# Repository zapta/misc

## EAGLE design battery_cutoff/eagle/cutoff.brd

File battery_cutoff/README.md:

Arduino car battery monitor/cutoff.

This is a custom Arduino board that monitors and controsl 12V DC in car environment.
It contains an ATMEGA328P MCU that monitors the battery voltage and controls an output
relay. 

The Arduino sketch that I am using with this board detects engine cranking pattern on the 
battery line and disconnects the output voltage to the streaming BT adapter for 
1 second. This resets the BT adapter and causes it to pair with my phone (the 
12VDC socket in my car mentain power even after I turn the engine off which causes
the BT adapter not to pair with my phone when I come back to the car).

The board is not specific to this applictaion and with different sketch can do
other battery monitoring/cutoff operations.

The board is compatible with the Arduino IDE (it acts as an Arduino Mini Pro 5V 16Mhz).

The 3d subdirectory here includes a model for a 3d printable snap-on enclosure. You
can find there both the OpenSCAD source file and the gnerated STL file. The PCB 
is attached to the base of the encolsure using a double side 3M adhesive tape 
such as this one https://www.amazon.com/dp/B00OI6E0L2 .

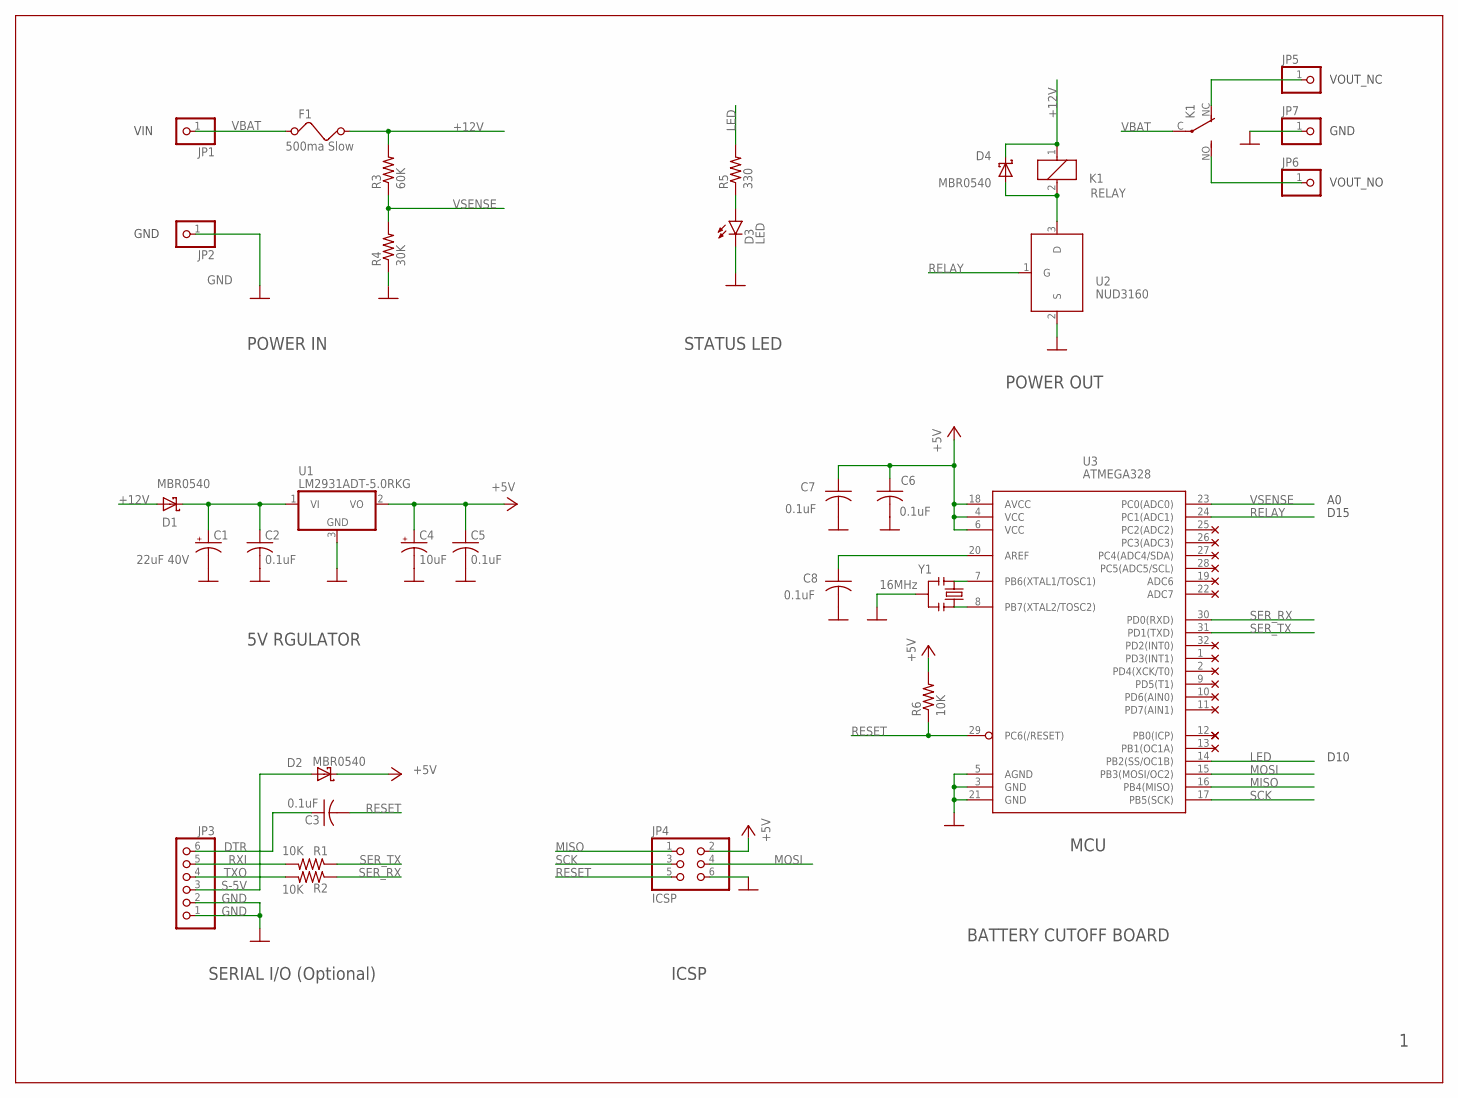
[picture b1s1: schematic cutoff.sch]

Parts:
C1: 22uF 40V; UD-6,3X5,8_NICHICON
C2, C3, C5, C6, C7, C8: 0.1uF; C0603K
C4: 10uF; A/3216-18R
D1, D2, D4: MBR0540; SOD123FL
D3: LED
F1: 500ma Slow; 1206
JP1, JP2, JP5, JP6, JP7: WIRE_PAD
JP3: PINHD-1X6; 1X06
JP4: ICSP; 2X03
K1: RELAY
R1, R2, R6: 10K; R0402
R3: 60K; R0402
R4: 30K; R0402
R5: 330; R0402
U1: LM2931ADT-5.0RKG; LDO
U2: NUD3160; SOT23
U3: ATMEGA328; TQFP32-08
Y1: 16MHz; RESONATOR-SMD

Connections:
+5V: C4.+, C5.1, C6.1, C7.1, D2.C, JP4.2, R6.2, U1.2 (VO), U3.4 (VCC), U3.6 (VCC), U3.18 (AVCC)
+12V: D1.A, D4.C, F1.2, K1.1, R3.2
AREF: C8.1, U3.20 (AREF)
DTR: C3.1, JP3.6
GND: C1.-, C2.2, C4.-, C5.2, C6.2, C7.2, C8.2, D3.K (C), JP2.1, JP3.1, JP3.2, JP4.6, JP7.1, R4.1, U1.3 (GND), U2.2 (S), U3.3 (GND), U3.5 (AGND), U3.21 (GND), Y1.2
LED: R5.2, U3.14 (PB2(SS/OC1B))
MISO: JP4.1, U3.16 (PB4(MISO))
MOSI: JP4.4, U3.15 (PB3(MOSI/OC2))
unnamed: D4.A, K1.2, U2.3 (D)
unnamed: D3.A, R5.1
unnamed: JP6.1, K1.NO (S)
unnamed: JP5.1, K1.NC (O)
unnamed: C1.+, C2.1, D1.C, U1.1 (VI)
RELAY: U2.1 (G), U3.24 (PC1(ADC1))
RESET: C3.2, JP4.5, R6.1, U3.29 (PC6(/RESET))
RXI: JP3.5, R1.2
S-5V: D2.A, JP3.3
SCK: JP4.3, U3.17 (PB5(SCK))
SER_RX: R2.1, U3.30 (PD0(RXD))
SER_TX: R1.1, U3.31 (PD1(TXD))
TXO: JP3.4, R2.2
VBAT: F1.1, JP1.1, K1.C
VSENSE: R3.1, R4.2, U3.23 (PC0(ADC0))
XTAL1: U3.7 (PB6(XTAL1/TOSC1)), Y1.3
XTAL2: U3.8 (PB7(XTAL2/TOSC2)), Y1.1

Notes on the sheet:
ICSP
SERIAL I/O (Optional)
MCU
STATUS LED
BATTERY CUTOFF BOARD
POWER IN
POWER OUT
5V RGULATOR
D15
D10
VOUT_NC
GND
VOUT_NO
VIN

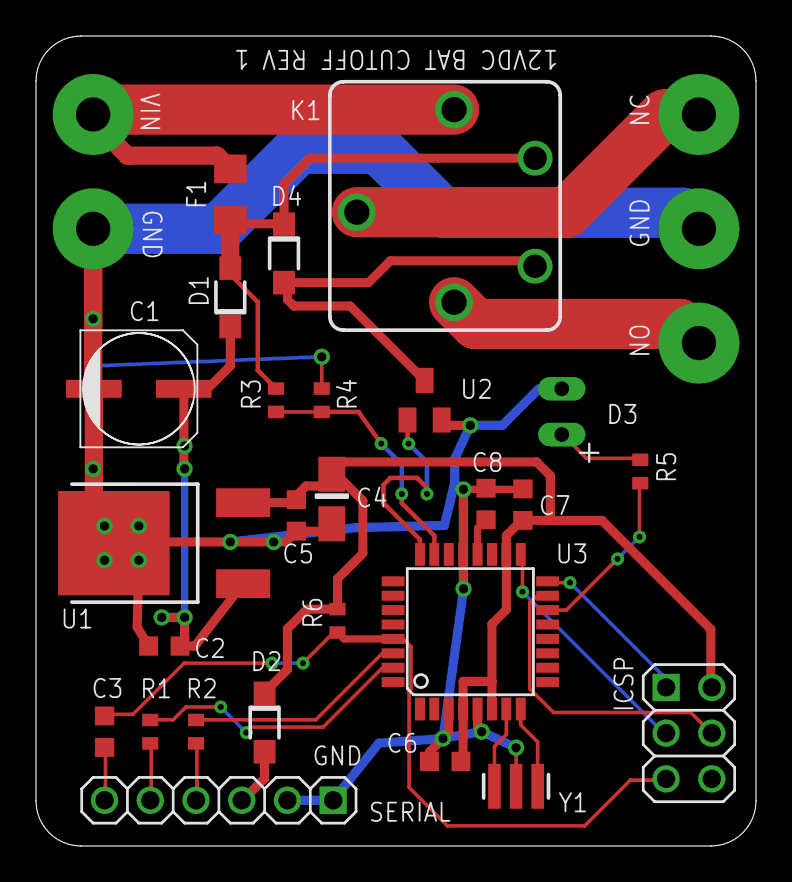
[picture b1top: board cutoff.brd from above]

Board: 2 copper layers, 40.0 x 45.0 mm, 31 parts (0 on the bottom side), 25 nets.

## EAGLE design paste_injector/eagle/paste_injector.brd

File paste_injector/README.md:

Arduino Motorized SMT Solder Paste Dispenser

3D model and general instructions are available on Thingiverse http://www.thingiverse.com/thing:1119914

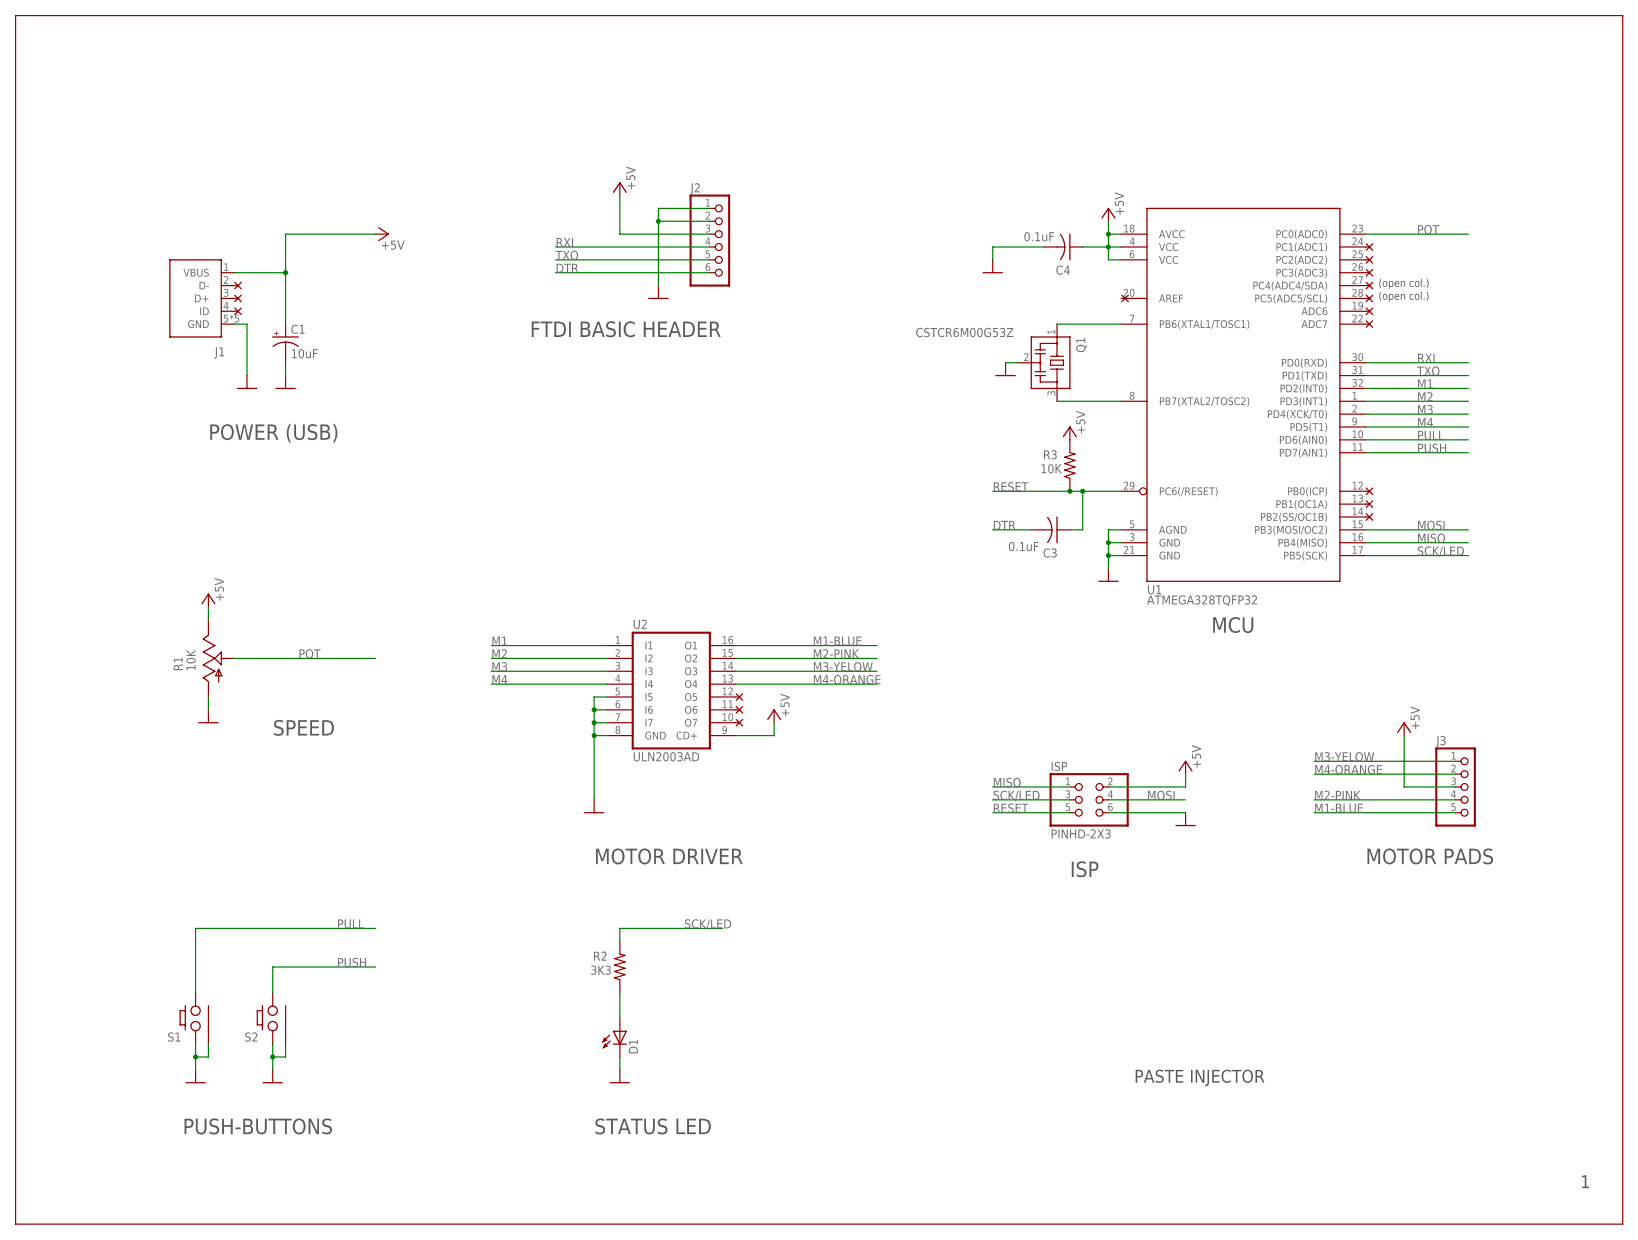
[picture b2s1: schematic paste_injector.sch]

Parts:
C1: 10uF; A/3216-18R
C3, C4: 0.1uF; C0603
D1: LED; LED0603
ISP: PINHD-2X3; 2X03
J1: USB; USB-MICRO-ZX62RD-AB-5P8
J2: PINHD-1X6; 1X06
J3: PINHD-1X5; 1X05
Q1: CSTCR6M00G53Z; CSTCR6M
R1: 10K; TRIMPOT
R2: 3K3; R0603
R3: 10K; R0603
S1, S2: PUSH_BUTTON
U1: ATMEGA328TQFP32; TQFP32-08
U2: ULN2003AD; SO16

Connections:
+5V: C1.+, C4.1, ISP.2, J1.1 (VBUS), J2.3, J3.3, R1.CW, R3.2, U1.4 (VCC), U1.6 (VCC), U1.18 (AVCC), U2.9 (CD+)
DTR: C3.2, J2.6
GND: C1.-, C4.2, D1.C, ISP.6, J1.5 (GND), J1.A (GND), J1.B (GND), J1.C (GND), J1.D (GND), J2.1, J2.2, Q1.2, R1.CCW, S1.A1 (1), S1.GND, S2.A1 (1), S2.GND, U1.3 (GND), U1.5 (AGND), U1.21 (GND), U2.5 (I5), U2.6 (I6), U2.7 (I7), U2.8 (GND)
M1: U1.32 (PD2(INT0)), U2.1 (I1)
M1-BLUE: J3.5, U2.16 (O1)
M2: U1.1 (PD3(INT1)), U2.2 (I2)
M2-PINK: J3.4, U2.15 (O2)
M3: U1.2 (PD4(XCK/T0)), U2.3 (I3)
M3-YELOW: J3.1, U2.14 (O3)
M4: U1.9 (PD5(T1)), U2.4 (I4)
M4-ORANGE: J3.2, U2.13 (O4)
MISO: ISP.1, U1.16 (PB4(MISO))
MOSI: ISP.4, U1.15 (PB3(MOSI/OC2))
unnamed: D1.A, R2.1
unnamed: Q1.1, U1.7 (PB6(XTAL1/TOSC1))
unnamed: Q1.3, U1.8 (PB7(XTAL2/TOSC2))
POT: R1.C, U1.23 (PC0(ADC0))
PULL: S1.B1 (2), U1.10 (PD6(AIN0))
PUSH: S2.B1 (2), U1.11 (PD7(AIN1))
RESET: C3.1, ISP.5, R3.1, U1.29 (PC6(/RESET))
RXI: J2.4, U1.30 (PD0(RXD))
SCK/LED: ISP.3, R2.2, U1.17 (PB5(SCK))
TXO: J2.5, U1.31 (PD1(TXD))

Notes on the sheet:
PASTE INJECTOR
ISP
POWER (USB)
SPEED
MOTOR DRIVER
MCU
MOTOR PADS
(open col.)
FTDI BASIC HEADER
STATUS LED
PUSH-BUTTONS

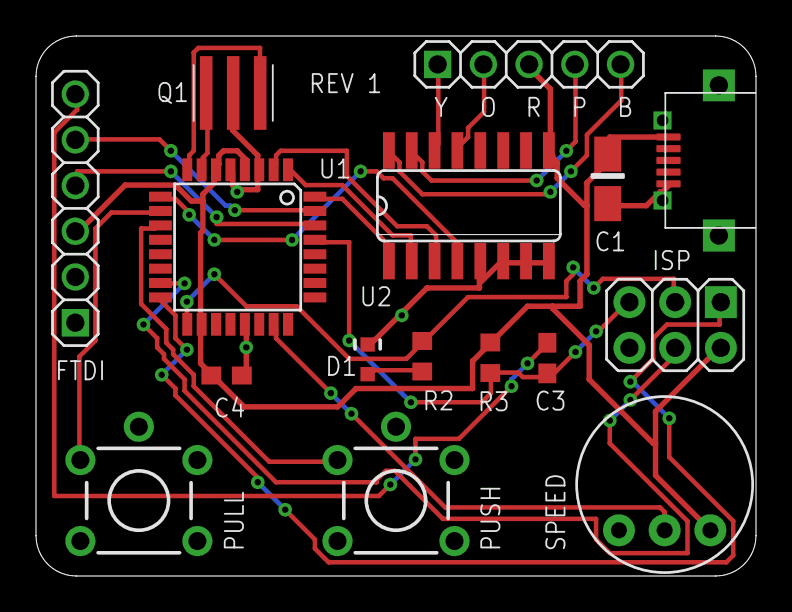
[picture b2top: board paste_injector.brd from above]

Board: 2 copper layers, 40.0 x 30.0 mm, 16 parts (0 on the bottom side), 23 nets.

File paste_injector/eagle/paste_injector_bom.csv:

Quantity,Description,Part Designators,Digikey Part Number,Manufacturer Name,Manufacturer Part Number,Comments1,3.3K 5% 1/10W 0603,R2,311-3.3KGRCT-ND,Yageo,RC0603JR-073K3L,1,10K 5%  1/10W 0603,R3,311-10KGRCT-ND,Yageo,RC0603JR-0710KL,2,0.1uf ceramic 10% 25V 0603,C3  C4,311-1344-1-ND,Yageo,CC0603KRX7R9BB104,1,LED Red 0603,D1,475-2512-1-ND,OSRAM Opto Semiconductors Inc.,LS Q976-NR-1,1,Micro USB connector,J1,H11611CT-ND,ZX62RD-AB-5P8,Hirose Electric Co Ltd,1,Trimpot 10K,R1,987-1167-ND,TT Electronics/BI,91AR10KLF,1,ATMEGA328P TQFP32,U1,ATMEGA328P-AURCT-ND,Atmel,ATMEGA328P-AUR,1,Resonator 16Mhz w/caps,Q1,535-10008-1-ND,Abracon LLC,AWSCR-16.00CV-T,1,ULN2003A  SOIC,U2,296-1368-1-ND,Texas Instruments,ULN2003ADR,2,Push Button,S1  S2,P8014S-ND,Panasonic Electronic Components,EVQ-PBC05R,1,Tantalum cap 10uF 10%  16V 1206,C1,399-3684-1-ND,Kemet,T491A106K010AT,1,5V bipolar geared stepper motor ,,,,28BYJ-48,Ebay7,Taper M4 heat threaded insert,,,McMaster,94180a353,2,M3 10mm socket head cup screw,,,McMaster,91274a105,Generic2,M3 nut,,,McMaster,94150a325,Generic4,M4 10mm socket head cup screw,,,McMaster,91274A117,Generic1,M4 0.7 x 64mm threaded rod,,,McMaster,90024a222,Cut to length1,10ml luer lock syringe,,,BD,REF309604,"Bectron, Dickinson"

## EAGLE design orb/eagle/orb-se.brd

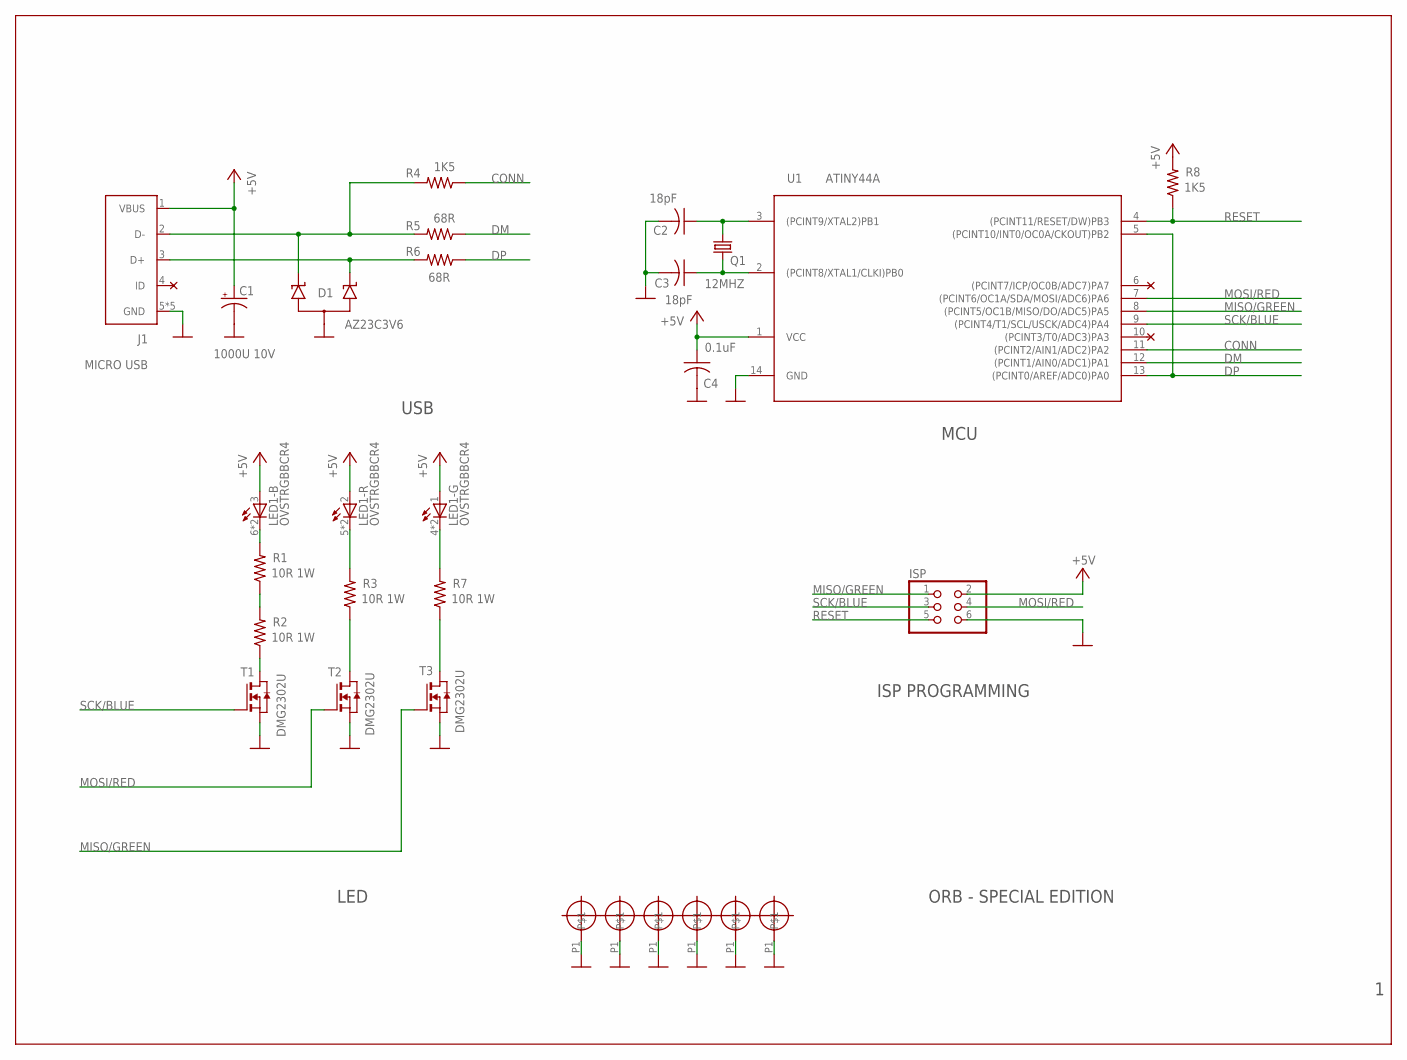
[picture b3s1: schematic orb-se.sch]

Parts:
C1: 1000U 10V; 153CLV-1010
C2, C3: 18pF; C0805
C4: 0.1uF; C0805
D1: AZ23C3V6; SOT23
ISP: PINHD-2X3; 2X03
J1: MICRO USB; USB-MICRO
LED1: OVSTRGBBCR4
MH$1, MH$2, MH$3, MH$4, MH$5, MH$6: MOUNTING_HOLE
Q1: 12MHZ; CRYSTAL
R1, R2, R3, R7: 10R 1W; R2512W
R4, R8: 1K5; R0805
R5, R6: 68R; R0805
T1, T2, T3: DMG2302U; SOT-23
U1: ATINY44A; SOIC14

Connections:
+5V: C1.+, C4.1, ISP.2, J1.1 (VBUS), LED1.1 (A), LED1.2 (A), LED1.3 (A), R8.2, U1.1 (VCC)
CONN: R4.1, U1.11 ((PCINT2/AIN1/ADC2)PA2)
DM: R5.1, U1.12 ((PCINT1/AIN0/ADC1)PA1)
DP: R6.1, U1.5 ((PCINT10/INT0/OC0A/CKOUT)PB2), U1.13 ((PCINT0/AREF/ADC0)PA0)
GND: C1.-, C2.2, C3.2, C4.2, D1.3 (AA), ISP.6, J1.5 (GND), J1.G1 (GND), J1.G2 (GND), J1.G3 (GND), J1.G4 (GND), MH$1.P1, MH$2.P1, MH$3.P1, MH$4.P1, MH$5.P1, MH$6.P1, T1.2 (S), T2.2 (S), T3.2 (S), U1.14 (GND)
MISO/GREEN: ISP.1, T3.3 (G), U1.8 ((PCINT5/OC1B/MISO/DO/ADC5)PA5)
MOSI/RED: ISP.4, T2.3 (G), U1.7 ((PCINT6/OC1A/SDA/MOSI/ADC6)PA6)
unnamed: C2.1, Q1.2, U1.3 ((PCINT9/XTAL2)PB1)
unnamed: C3.1, Q1.1, U1.2 ((PCINT8/XTAL1/CLKI)PB0)
unnamed: R1.1, R2.2
unnamed: D1.1 (K1), J1.2 (D-), R4.2, R5.2
unnamed: D1.2 (K2), J1.3 (D+), R6.2
unnamed: LED1.6 (C), LED1.6@1 (C), R1.2
unnamed: LED1.5 (C), LED1.5@1 (C), R3.2
unnamed: LED1.4 (C), LED1.4@1 (C), R7.2
unnamed: R2.1, T1.1 (D)
unnamed: R3.1, T2.1 (D)
unnamed: R7.1, T3.1 (D)
RESET: ISP.5, R8.1, U1.4 ((PCINT11/RESET/DW)PB3)
SCK/BLUE: ISP.3, T1.3 (G), U1.9 ((PCINT4/T1/SCL/USCK/ADC4)PA4)

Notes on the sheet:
ORB - SPECIAL EDITION
USB
MCU
ISP PROGRAMMING
LED

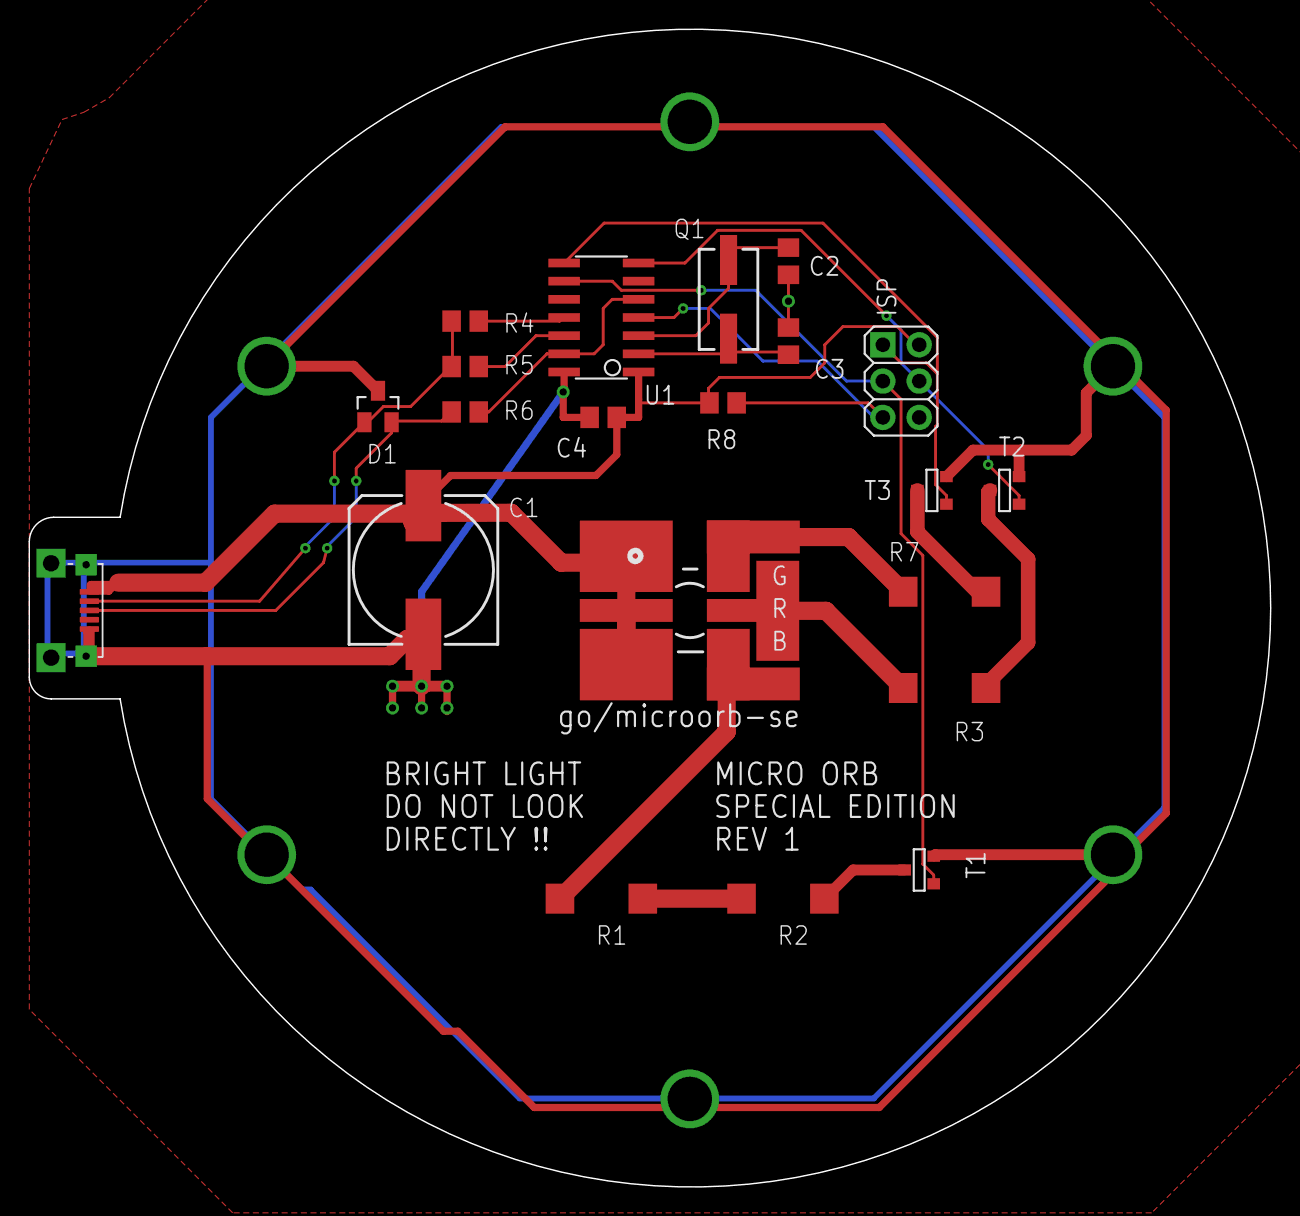
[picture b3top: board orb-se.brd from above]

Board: 2 copper layers, 86.8 x 80.9 mm, 27 parts (0 on the bottom side), 20 nets.

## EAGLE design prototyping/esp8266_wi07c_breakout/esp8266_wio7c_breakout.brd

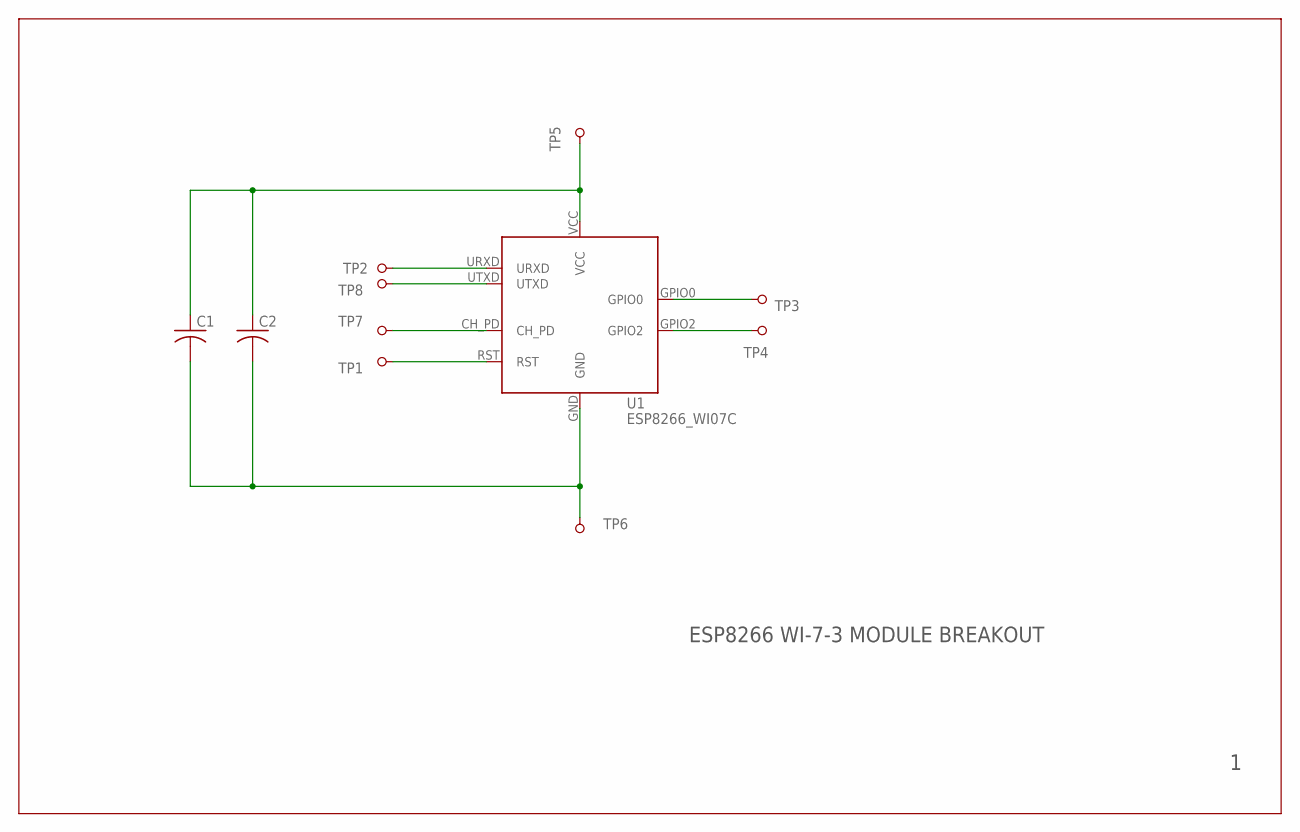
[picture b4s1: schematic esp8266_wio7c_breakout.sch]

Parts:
C1, C2: CAPACITORC0603K; C0603K
TP1, TP2, TP3, TP4, TP5, TP7, TP8: PINHD-1X1; 1X01
TP6: PINHD-1X1-FIRST; 1X01_FIRST
U1: ESP8266_WI07C

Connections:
CH_PD: TP7.1, U1.CH_PD
GND: C1.2, C2.2, TP6.1, U1.GND
GPIO0: TP3.1, U1.GPIO0
GPIO2: TP4.1, U1.GPIO2
RST: TP1.1, U1.RST
URXD: TP2.1, U1.URXD
UTXD: TP8.1, U1.UTXD
VCC: C1.1, C2.1, TP5.1, U1.VCC

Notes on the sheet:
ESP8266 WI-7-3 MODULE BREAKOUT

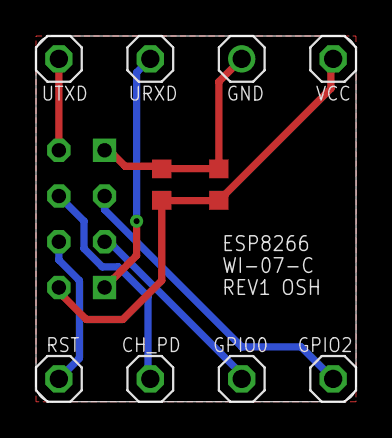
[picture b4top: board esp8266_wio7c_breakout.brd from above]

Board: 2 copper layers, 17.8 x 20.3 mm, 11 parts (0 on the bottom side), 8 nets.

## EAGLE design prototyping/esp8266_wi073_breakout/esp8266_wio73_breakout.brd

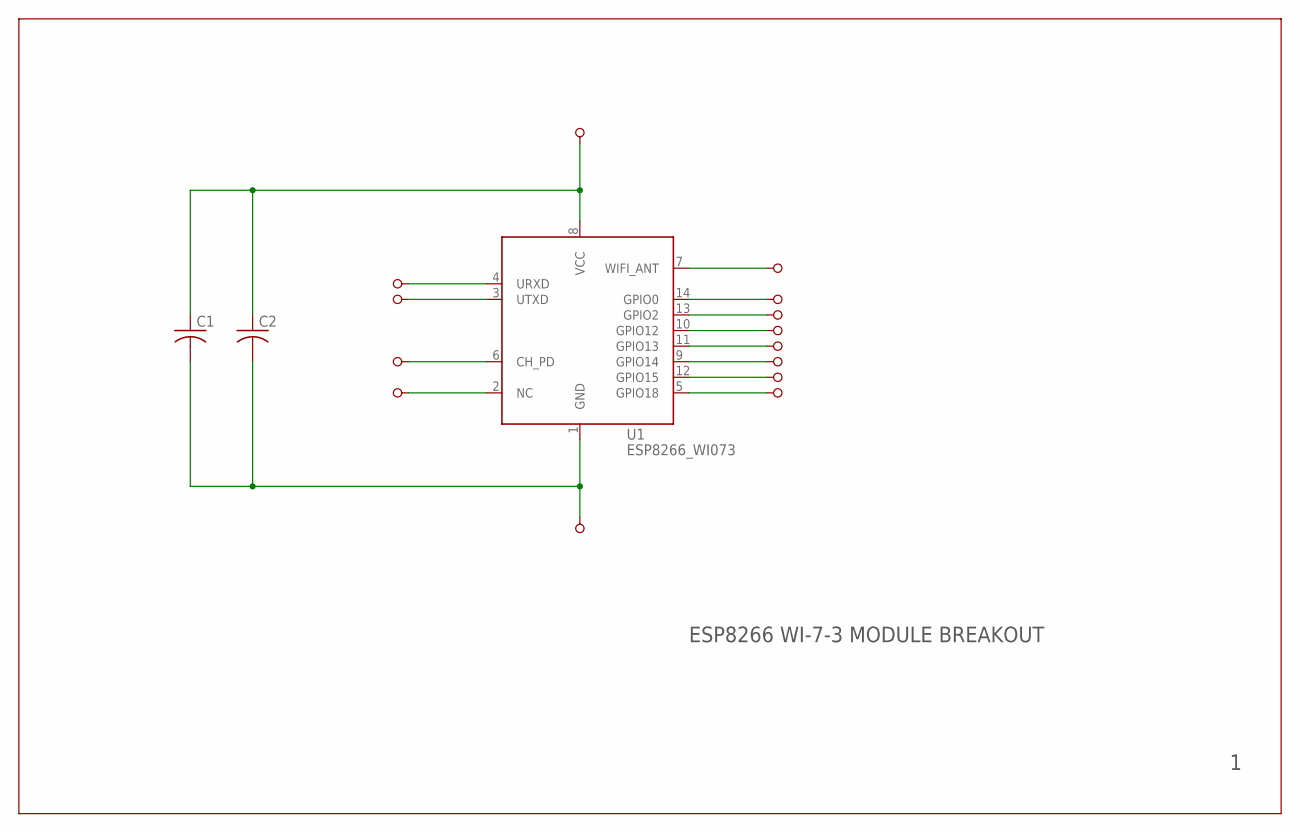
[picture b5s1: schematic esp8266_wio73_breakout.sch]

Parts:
C1, C2: CAPACITORC0603K; C0603K
TP1: PINHD-1X1-FIRST; 1X01_FIRST
TP2, TP3, TP4, TP5, TP6, TP7, TP8, TP9, TP10, TP11, TP12, TP13, TP14: PINHD-1X1; 1X01
U1: ESP8266_WI073

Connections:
GND: C1.2, C2.2, TP1.1, U1.1 (GND)
unnamed: TP4.1, U1.4 (URXD)
unnamed: TP3.1, U1.3 (UTXD)
unnamed: TP6.1, U1.6 (CH_PD)
unnamed: TP2.1, U1.2 (NC)
unnamed: TP7.1, U1.7 (WIFI_ANT)
unnamed: TP14.1, U1.14 (GPIO0)
unnamed: TP13.1, U1.13 (GPIO2)
unnamed: TP10.1, U1.10 (GPIO12)
unnamed: TP11.1, U1.11 (GPIO13)
unnamed: TP9.1, U1.9 (GPIO14)
unnamed: TP12.1, U1.12 (GPIO15)
unnamed: TP5.1, U1.5 (GPIO18)
VCC: C1.1, C2.1, TP8.1, U1.8 (VCC)

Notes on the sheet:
ESP8266 WI-7-3 MODULE BREAKOUT

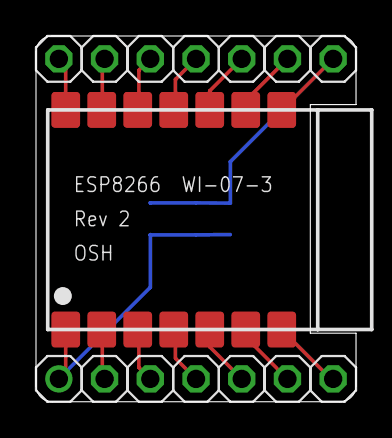
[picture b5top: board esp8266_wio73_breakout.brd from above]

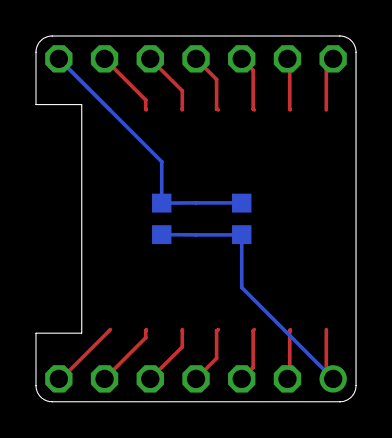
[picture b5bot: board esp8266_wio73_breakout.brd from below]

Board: 2 copper layers, 17.8 x 20.3 mm, 17 parts (2 on the bottom side), 14 nets.

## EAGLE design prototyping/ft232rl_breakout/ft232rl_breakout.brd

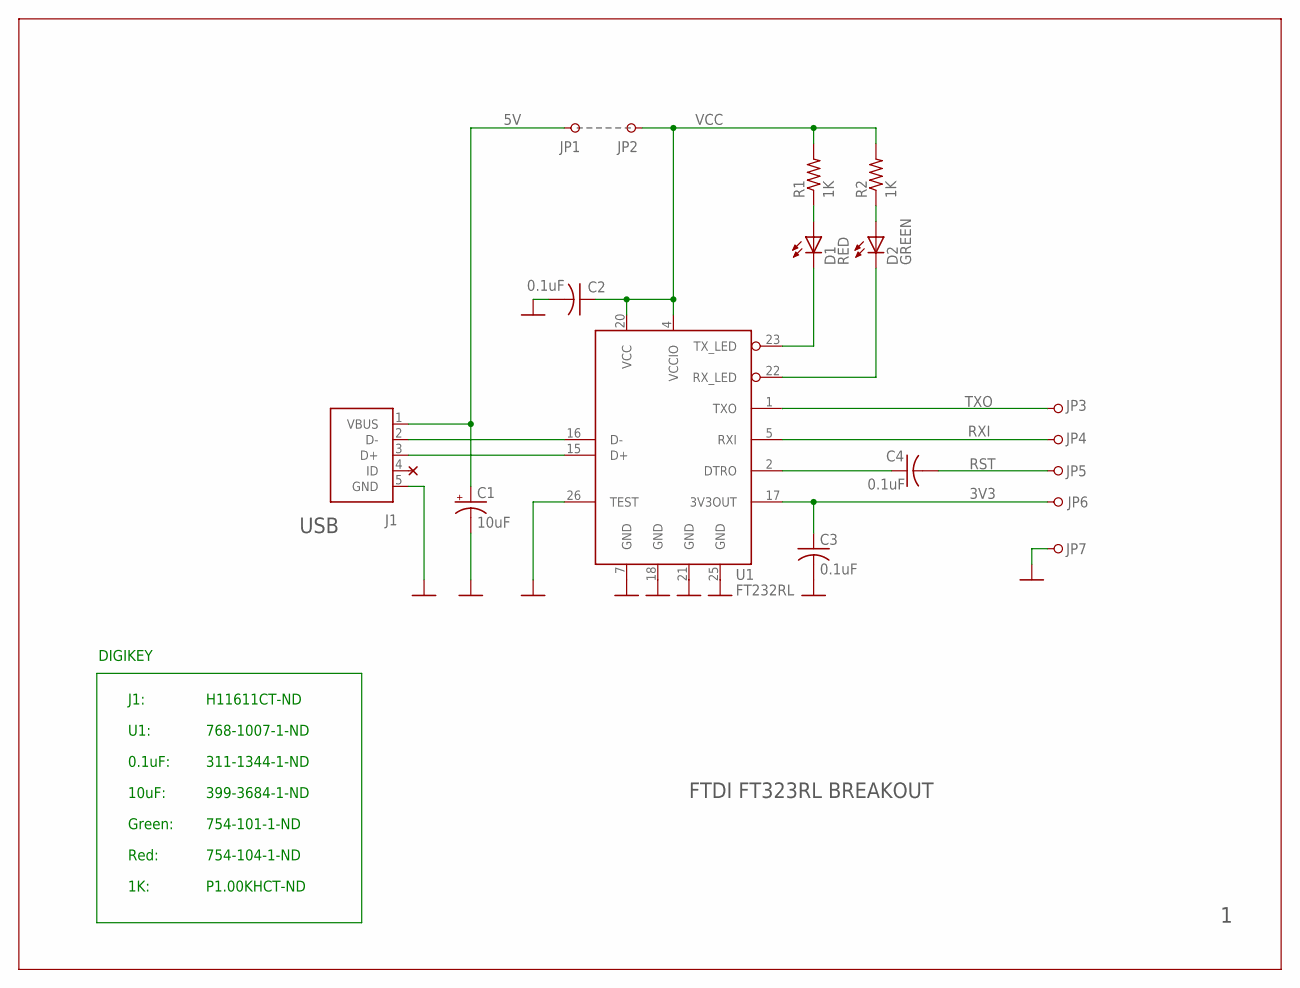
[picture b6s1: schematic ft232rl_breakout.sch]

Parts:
C1: 10uF; A/3216-18R
C2, C3, C4: 0.1uF; C0402K
D1: RED; LED_0402
D2: GREEN; LED_0402
J1: USB; USB-MICRO-ZX62RD-AB-5P8
JP1, JP2, JP3, JP4, JP5, JP6, JP7: PINHD-1X1; 1X01
R1, R2: 1K; R0402
U1: FT232RL; SSOP28DB

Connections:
3V3: C3.1, JP6.1, U1.17 (3V3OUT)
5V: C1.+, J1.1 (VBUS), JP1.1
GND: C1.-, C2.2, C3.2, J1.5 (GND), JP7.1, U1.7 (GND), U1.18 (GND), U1.21 (GND), U1.25 (GND), U1.26 (TEST)
unnamed: D1.C, U1.23 (TX_LED)
unnamed: D2.C, U1.22 (RX_LED)
unnamed: D1.A, R1.1
unnamed: D2.A, R2.1
unnamed: J1.3 (D+), U1.15 (D+)
unnamed: C4.1, U1.2 (DTRO)
unnamed: J1.2 (D-), U1.16 (D-)
RST: C4.2, JP5.1
RXI: JP4.1, U1.5 (RXI)
TXO: JP3.1, U1.1 (TXO)
VCC: C2.1, JP2.1, R1.2, R2.2, U1.4 (VCCIO), U1.20 (VCC)

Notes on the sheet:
FTDI FT323RL BREAKOUT
USB
J1:
U1:
0.1uF:
10uF:
Green:
Red:
1K:
H11611CT-ND
768-1007-1-ND
311-1344-1-ND
399-3684-1-ND
754-101-1-ND
754-104-1-ND
P1.00KHCT-ND
DIGIKEY

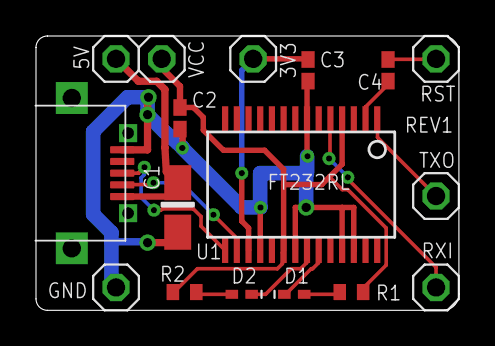
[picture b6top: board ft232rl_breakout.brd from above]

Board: 2 copper layers, 23.5 x 15.2 mm, 17 parts (0 on the bottom side), 14 nets.

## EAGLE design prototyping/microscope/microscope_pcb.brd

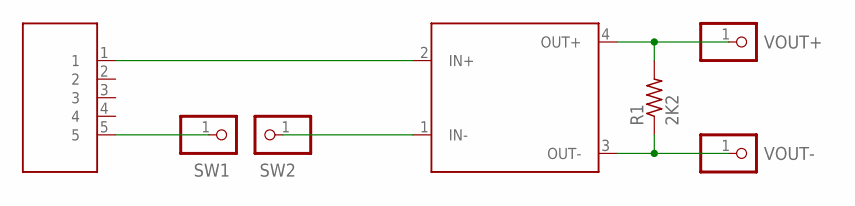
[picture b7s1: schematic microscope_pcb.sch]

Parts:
R1: 2K2; R0805
SW1, SW2: PINHD-1X1; 1X01
U$1: DC_DC
U$2: USB_CONNECTOR
VOUT+: PINHD-1X1; 1X01
VOUT-: PINHD-1X1; 1X01

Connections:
unnamed: R1.2, U$1.4 (OUT+), VOUT+.1
unnamed: R1.1, U$1.3 (OUT-), VOUT-.1
unnamed: U$1.2 (IN+), U$2.1
unnamed: SW1.1, U$2.5
unnamed: SW2.1, U$1.1 (IN-)

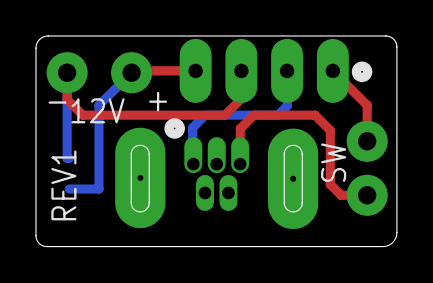
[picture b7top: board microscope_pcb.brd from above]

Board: 2 copper layers, 20.1 x 11.7 mm, 7 parts (1 on the bottom side), 5 nets.

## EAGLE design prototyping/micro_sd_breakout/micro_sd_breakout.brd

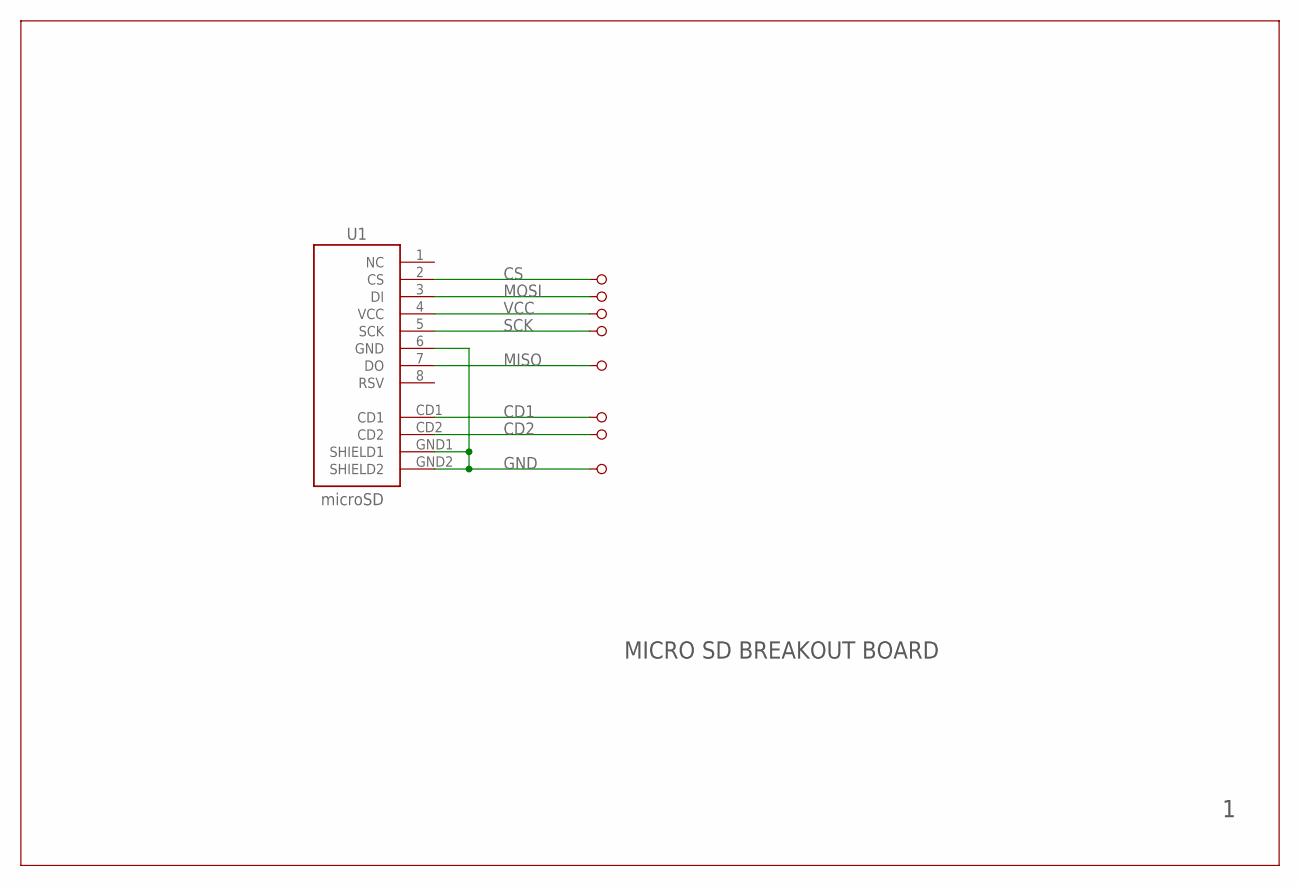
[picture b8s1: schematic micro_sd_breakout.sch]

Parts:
JP1, JP2, JP3, JP4, JP5, JP6, JP7, JP8: PINHD-1X1; 1X01
U1: microSD; MICRO-SD-SOCKET-PP

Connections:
CD1: JP6.1, U1.CD1
CD2: JP7.1, U1.CD2
CS: JP1.1, U1.2 (CS)
GND: JP8.1, U1.6 (GND), U1.GND1 (SHIELD1), U1.GND2 (SHIELD2)
MISO: JP5.1, U1.7 (DO)
MOSI: JP2.1, U1.3 (DI)
SCK: JP4.1, U1.5 (SCK)
VCC: JP3.1, U1.4 (VCC)

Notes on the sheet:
MICRO SD BREAKOUT BOARD

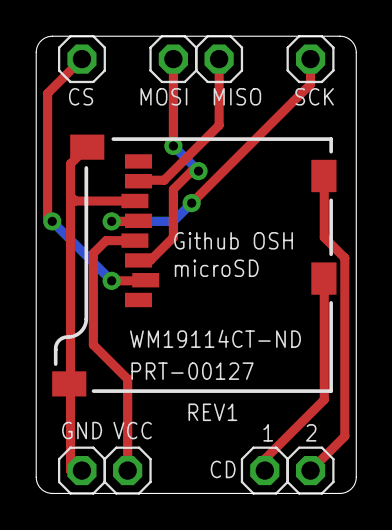
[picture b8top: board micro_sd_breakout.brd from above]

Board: 2 copper layers, 17.8 x 25.4 mm, 9 parts (0 on the bottom side), 8 nets.

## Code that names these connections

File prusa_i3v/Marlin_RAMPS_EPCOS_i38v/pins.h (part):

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*                        ATMega644
*
*                        +---\/---+
*            (D 0) PB0  1|        |40  PA0 (AI 0 / D31)
*            (D 1) PB1  2|        |39  PA1 (AI 1 / D30)
*       INT2 (D 2) PB2  3|        |38  PA2 (AI 2 / D29)
*        PWM (D 3) PB3  4|        |37  PA3 (AI 3 / D28)
*        PWM (D 4) PB4  5|        |36  PA4 (AI 4 / D27)
*       MOSI (D 5) PB5  6|        |35  PA5 (AI 5 / D26)
*       MISO (D 6) PB6  7|        |34  PA6 (AI 6 / D25)
*        SCK (D 7) PB7  8|        |33  PA7 (AI 7 / D24)
*                  RST  9|        |32  AREF
*                  VCC 10|        |31  GND 
*                  GND 11|        |30  AVCC
*                XTAL2 12|        |29  PC7 (D 23)
*                XTAL1 13|        |28  PC6 (D 22)
*       RX0 (D 8)  PD0 14|        |27  PC5 (D 21) TDI
*       TX0 (D 9)  PD1 15|        |26  PC4 (D 20) TDO
*  INT0 RX1 (D 10) PD2 16|        |25  PC3 (D 19) TMS
*  INT1 TX1 (D 11) PD3 17|        |24  PC2 (D 18) TCK
*       PWM (D 12) PD4 18|        |23  PC1 (D 17) SDA
*       PWM (D 13) PD5 19|        |22  PC0 (D 16) SCL
*       PWM (D 14) PD6 20|        |21  PD7 (D 15) PWM
*                        +--------+
*
****************************************************************************************/
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
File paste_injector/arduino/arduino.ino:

// Controller the solder paste injector.

// For motor pin connection see motor_io.cpp.

#include "motor.h"

// Finite state machine states. Using 8bit enums.
namespace states {
  // Not moving, motor is on.
  static const uint8_t IDLE = 0;
  // Moving forward as long as the forward button is pressed.
  // Speed is controlled by the potentiometer.
  static const uint8_t FORWARD = 1;
  // Moving backward at a fast speed as long as the Backward button
  // is pressed.
  static const uint8_t BACKWARD = 3;
  // Same as IDLE but motor coils are not energized.
  static const uint8_t SLEEP = 4;
};

static uint8_t state = states::IDLE;

// Arduino pin for nnboard LED. For debugging. Active high.
const int kLedPin = 13;

// Arduino potentiometer analog input pin.
static const int kPotPin = A0;

// Arduino input pin for the forward (push) button. Active low.
static const int kForwardButtonPin = 7;

// Arduino input pin for the backward (pull) button. Active low.
static const int kBackwardButtonPin = 6;

// After this idle time, the power to the motor is
// disconnected. 
static const uint32_t kSleepTimeMillis =20*1000;

// Speeds in steps/sec.
static const int kBackwardSpeed = 500;

// Time in millis since entering the current state.
static uint32_t current_state_start_time_millis = 0;

// TODO: why do we need this to compile. The function is just below.
//static void setState(uint8_t newState);

// A common function to change state.
static void setState(uint8_t newState) {
  if (newState != state) {
    Serial.print(state);
    Serial.print(" --> ");
    Serial.println(newState);
    state = newState;
    current_state_start_time_millis = millis();
  }
}

static inline uint32_t millisInCurrentState() {
  return (millis() - current_state_start_time_millis);
}

// Using this as a poor man debouncing in states that we entered
// due to a button action.
static inline boolean debouncingDelay() {
   return millisInCurrentState() >= 25;
}

// Consts of a single segment of the pot value mapping function.
struct MapSegment {
  const int inMin;
  const int inMax;
  const int outMin;
  const int outMax;
};

// Consts for all the segments of the pot value mapping function.
static const MapSegment kMapSegments[] = {
  {  0,   128,  1,    2},
  {128,   256,  2,    4},
  {256,   384,  4,   10},
  {384,   512, 10,   22},
  {512,  640,  22,   48},
  {640,  768,  48,  105},
  {768,  896, 105,  229},
  {896, 1023, 229,  500},
};

// NUmber of segments in kMapSegments.
const int kNumMapSegments = sizeof(kMapSegments) / sizeof(kMapSegments[0]);

// Map pot value to speed. We use an aproximation of a logarithmic
// function using the linear segments in kMapSegments.
int mapPotValue(int potValue) {
  potValue = constrain(potValue, 0, 1023);
  for (int i = 0; i < kNumMapSegments; i++) {
    const MapSegment& s = kMapSegments[i];
    if (potValue <= s.inMax) {
      // TODO: precompute dIn and dOut.
      return (int) (((long)potValue - s.inMin) * (s.outMax - s.outMin) / (s.inMax - s.inMin)) + s.outMin;
    }
  }
  return kMapSegments[kNumMapSegments - 1].outMax;
}

// These two are updated each time readPostAsSpeed() is called.
static unsigned long timeLastPotReadMillis = 0;
static int lastPotValueAsSpeed = 0;

// Read pot value and return it mapped to speed.
static int readPotAsSpeed() {
  timeLastPotReadMillis = millis();
  const int potValue = analogRead(kPotPin);
  lastPotValueAsSpeed = mapPotValue(potValue);
  Serial.print("S:");
  Serial.println(lastPotValueAsSpeed);
  return lastPotValueAsSpeed;
}

inline long millisSinceLastPotRead() {
  return millis() - timeLastPotReadMillis;
}

inline bool isForwardButtonPressed() {
  // TODO: debounce.
  //
  // Active low.
  return !digitalRead(kForwardButtonPin);
}

inline bool isBackwardButtonPressed() {
  // TODO: debounce.
  //
  // Active low.
  return !digitalRead(kBackwardButtonPin);
}

// Arduino initialization function.
void setup() {
  Serial.begin(115200);
  
  pinMode(kLedPin, OUTPUT);

  pinMode(kForwardButtonPin, INPUT_PULLUP);
  pinMode(kBackwardButtonPin, INPUT_PULLUP);

  motor::setup();
  motor::setSpeed(0, true);
}

// Arduino main loop function.
void loop() {  
  // Update the motor outputs as needed.
  motor::loop();

  // TODO: have a more interesting LED pattern. Currently it's on iff
  // in a state that turns the motor.
  digitalWrite(kLedPin, motor::isNonZeroSpeed());

  // Here when last motion operation is completed.
  switch (state) {
    case states::IDLE:
      if (millisInCurrentState() >= kSleepTimeMillis) {
        motor::sleep();
        setState(states::SLEEP);
        return;
      }
      // Handle buttons unly after minimal debouncing delay.
      if (!debouncingDelay()) {
        return;
      }
      //
      // Handle Forward button press.
      if (isForwardButtonPressed()) {
        motor::setSpeed(readPotAsSpeed(), true);
        setState(states::FORWARD);
        return;
      }
      // Handle Backward button press.
      if (isBackwardButtonPressed()) {
        motor::setSpeed(kBackwardSpeed, false);
        setState(states::BACKWARD);
        return;
      }
      break;

    case states::FORWARD:
      // Handle Forward button release.
      if (!isForwardButtonPressed() && debouncingDelay()) {
        motor::setSpeed(0, true);
        setState(states::IDLE);
        return;
      }
      // Handle pot changes.
      if (millisSinceLastPotRead() >= 250) {
        motor::setSpeed(readPotAsSpeed(), true);
      }
      break;

    case states::BACKWARD:
      // Handle Backward button release.
      if (!isBackwardButtonPressed() && debouncingDelay()) {
        motor::setSpeed(0, true);
        setState(states::IDLE);
        return;
      }
      break;

    case states::SLEEP:
      if (isForwardButtonPressed() || isBackwardButtonPressed()) {
        motor::setSpeed(0, false);
        setState(states::IDLE);
        return;  
      }
      break;

    default:
      // Should never happend.
      Serial.println("Unknown state");
      // This also prints the unknown state.
      setState(states::IDLE);
  }
}
